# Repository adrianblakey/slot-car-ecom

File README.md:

# The Remora&trade; 1 - Slot Car eCom

This repo contains a [KiCad](https://www.kicad.org/) design, documentation and ancillary artifacts for a slot car brushless motor electronic commutator or "eCom", also known as an Electronic Speed Controller (ESC).

If you are looking for our latest board - the Remora&trade; 2 - you find it here: https://github.com/aartech-dev/Remora2 Please note this is in a different github organization to where we'll eventually move this repo.

All the intellectual property herein is released under a modified [creative commons license](https://github.com/adrianblakey/slot-car-ecom/blob/main/AART_Remora_eCom_License_v1.2.pdf). Under the terms of this license you are free to use everything you find here and make your own eCom from the distributed files as long as you comply with certain rules that are spelled out in the above document. We hope that by doing so we'll stimulate innovation and experimentation. If you have suggestions for improvement please file a bug report and tell us about it. 

There is a [remora1 discussion channel on Discord](https://discord.gg/e3FdfGwk2X) to provide feedback. Also, a good place to get help is the [ESCape32 slot car discord channel](https://discord.gg/XNwYPM7E). ESCape32 is the firmware we have used to run this eCom it's also open source and you'll find it on [github too.](https://github.com/neoxic/ESCape32)

There is nothing stopping you from making your own copies of this eCom. As a hobbyist, or manufacturer everything is here to help you do that. As a hobbyist and with a bit of effort you can make very small quantities at very reasonable cost.

If you choose to manufactuer the parts and sell them as a finished product we ask that you negotiate a small royalty payment with us. These designs are open but not free - all the intellectual property (IP) in this repo. belongs to us. If you have a product you are selling that's based on our IP and it's out there in the marketplace we'll know about it because it's a small (slot car) world. If you are making and selling our designs please talk to us and be up front about it. We incur some real expenses to create this and we want to continue innovating. To do that requires some income and that comes from making parts from the design and selling them.

You should also know that if you are making and selling parts it's your responsibility to support the people who buy them. We are more than happy to help you do that if we are receiving some compensation from you. We've been very generous with the amount of information that we have shared publically on this WiKi to make support simpler. If you choose to republish this information you are under obligation of our [License](https://github.com/adrianblakey/slot-car-ecom/blob/main/AART_Remora_eCom_License_v1.2.pdf) to acknowledge its source. 

We also ask that nothing here is used for military purposes. This also applies to the ESCape32 firmware.

Please refer to the [WiKi for detailed information](https://github.com/adrianblakey/slot-car-ecom/wiki).

Communicate with us on the slot-car channel of the [ESCape32 Discord server.](https://discord.gg/b9SHzh3eSR)

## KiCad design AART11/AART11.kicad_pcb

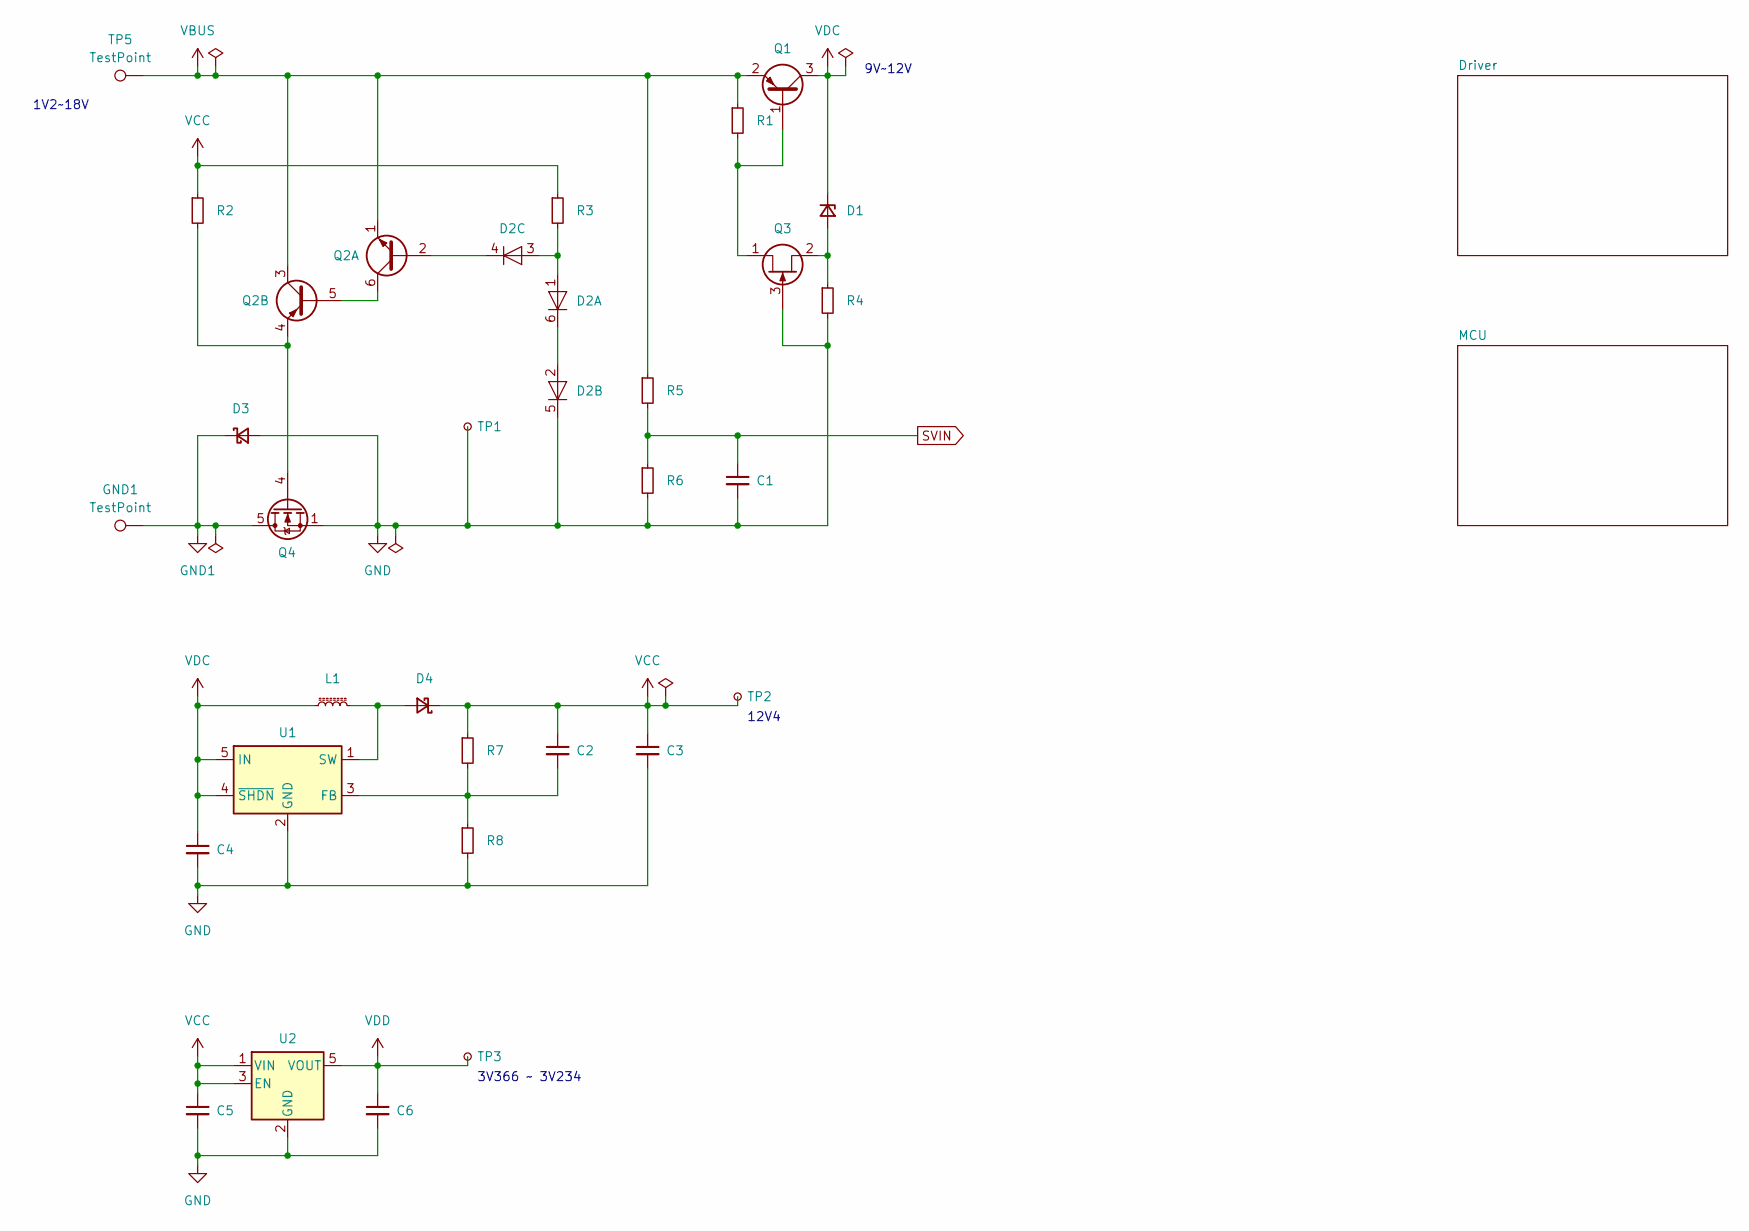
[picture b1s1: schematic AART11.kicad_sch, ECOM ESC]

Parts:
C1: 100nF; C_0402_1005Metric; Rating X7R - 16V - ±10%; JLCPCB Part # C1525
C2: 10pF; C_0402_1005Metric; Rating C0G - 50V - ±5%; JLCPCB Part # C32949
C3, C5: 1uF; C_0603_1608Metric; Rating X5R - 50V - ±10%; JLCPCB Part # C15849
C4, C6: 2.2uF; C_0603_1608Metric; Rating X5R - 16V - ±10%; JLCPCB Part # C23630
D1: BZX584C8V2; D_SOD-523; JLCPCB Part # C2991969
D2: MMBD4448HTW; SOT-363_SC-70-6; JLCPCB Part # C435910
D3: PMEG3030EP; D_SOD-128; JLCPCB Part # C255587
D4: RB521SM-40T2R; D_SOD-523; JLCPCB Part # C253516
GND1: TestPoint; TestPoint_Pad_2.5x2.5mm
L1: 10uH; L_Sunltech_SLW2010P; Rating 750mA - ±20%; JLCPCB Part # C207862
Q1: FMMT718; SOT-23; JLCPCB Part # C2910189
Q2: EMZ1T2R; SOT-563; JLCPCB Part # C510332
Q3: MMBFJ309; SOT-23; JLCPCB Part # C58012
Q4: JMSL0302AU; VSON-8_3.3x3.3mm_P0.65mm_NexFET; JLCPCB Part # C2890409
R1, R5, R8: 10k; R_0402_1005Metric; Rating 62.5mW - ±1%; JLCPCB Part # C25744
R2, R6: 2k2; R_0402_1005Metric; Rating 62.5mW - ±1%; JLCPCB Part # C25879
R3: 4k7; R_0402_1005Metric; Rating 62.5mW - ±1%; JLCPCB Part # C25900
R4: 330R; R_0402_1005Metric; Rating 62.5mW - ±1%; JLCPCB Part # C25104
R7: 91k; R_0402_1005Metric; Rating 62.5mW - ±1%; JLCPCB Part # C4147
TP1, TP2, TP3: TestPoint_Small; TestPoint_Pad_D1.0mm
TP5: TestPoint; TestPoint_Pad_2.5x2.5mm
U1: AP3015KTR-G1; SOT-23-5; JLCPCB Part # C151334
U2: AP2210K-3.3TRG1; SOT-23-5; JLCPCB Part # C176959

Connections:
GND: C1.2, C3.2, C4.2, C5.2, C6.2, D2.5 (K), D3.2 (A), Q3.3 (G), Q4.1 (S), Q4.2 (S), Q4.3 (S), R4.2, R6.2, R8.2, TP1.1, U1.2 (GND), U2.2 (GND); also elsewhere on the board
GND1: D3.1 (K), GND1.1, Q4.5 (D)
unnamed: D1.2 (A), Q3.2 (S), R4.1
unnamed: D2.1 (A), D2.3 (A), R3.2
unnamed: D2.2 (A), D2.6 (K)
unnamed: D2.4 (K), Q2.2 (B1)
unnamed: D4.2 (A), L1.2, U1.1 (SW)
unnamed: Q1.1 (B), Q3.1 (D), R1.2
unnamed: Q2.5 (B2), Q2.6 (C1)
unnamed: Q2.4 (E2), Q4.4 (G), R2.2
unnamed: C2.2, R7.2, R8.1, U1.3 (FB)
SVIN: C1.1, R5.2, R6.1; also elsewhere on the board
VBUS: Q1.2 (E), Q2.1 (E1), Q2.3 (C2), R1.1, R5.1, TP5.1; also elsewhere on the board
VCC: C2.1, C3.1, C5.1, D4.1 (K), R2.1, R3.1, R7.1, TP2.1, U2.1 (VIN), U2.3 (EN); also elsewhere on the board
VDC: C4.1, D1.1 (K), L1.1, Q1.3 (C), U1.4 (~SHDN), U1.5 (IN)
VDD: C6.1, TP3.1, U2.5 (VOUT); also elsewhere on the board

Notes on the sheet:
3V366 ~ 3V234
9V~12V
1V2~18V
12V4

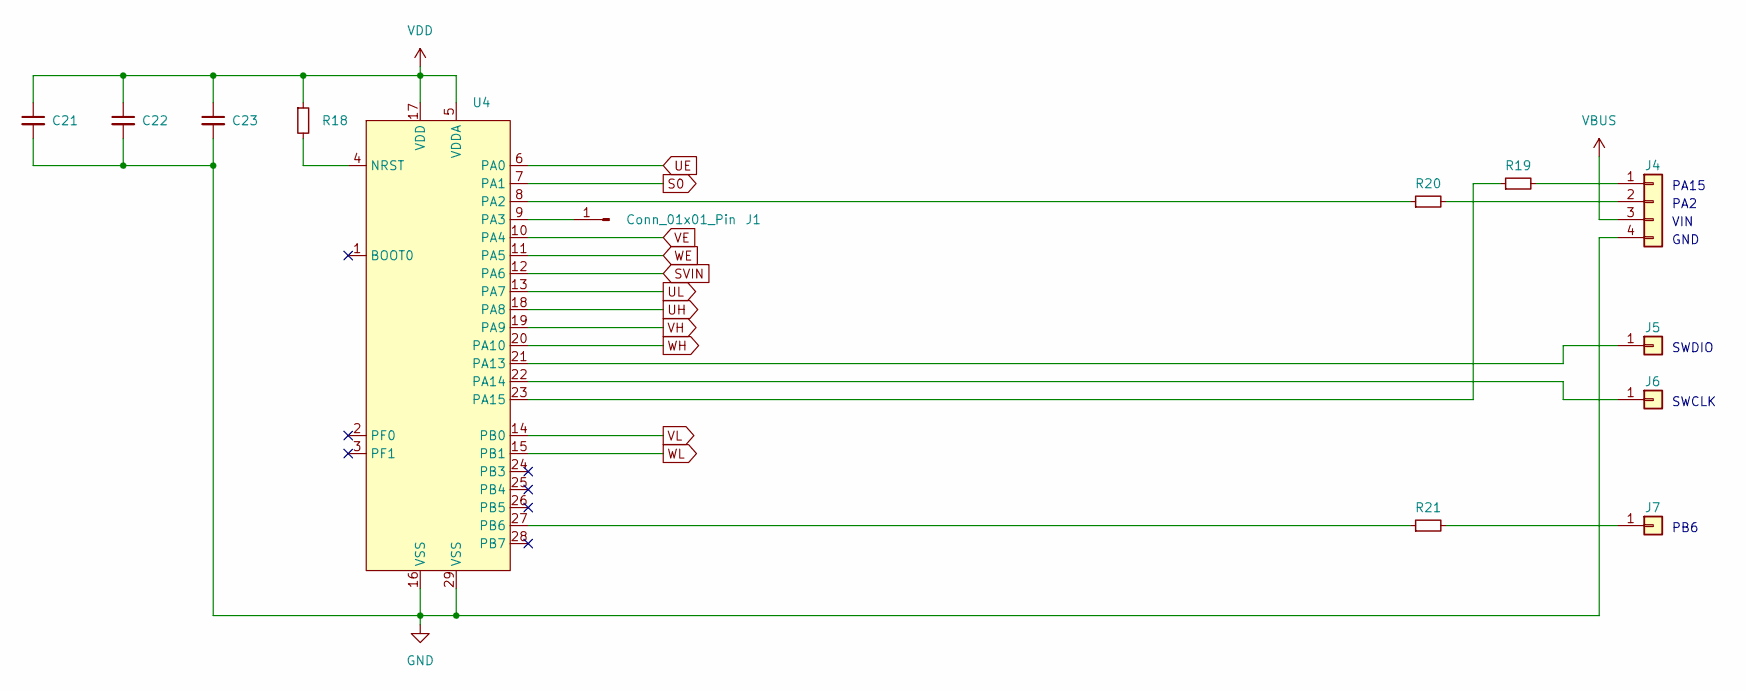
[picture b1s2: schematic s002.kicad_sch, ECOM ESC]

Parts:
C21: 10uF; C_0603_1608Metric; Rating X5R - 25V - ±20%; JLCPCB Part # C96446
C22, C23: 100nF; C_0402_1005Metric; Rating X7R - 16V - ±10%; JLCPCB Part # C1525
J1: Conn_01x01_Pin; Pad0.5
J4: Conn_01x04; HDG 1x04 P0.6 Horizontal; JLCPCB Part # C3008763
J5, J6, J7: Conn_01x01; TestPoint_Pad_1.0x1.0mm
R18: 10k; R_0402_1005Metric; Rating 62.5mW - ±1%; JLCPCB Part # C25744
R19, R20, R21: 1k; R_0402_1005Metric; Rating 62.5mW - ±1%; JLCPCB Part # C11702
U4: AT32F421G8U7; QFN-28-1EP_4x4mm_P0.4mm_EP2.6x2.6mm; JLCPCB Part # C2765098

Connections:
GND: C21.2, C22.2, C23.2, J4.4, U4.16 (VSS), U4.29 (VSS); also elsewhere on the board
unnamed: J1.1, U4.9 (PA3)
unnamed: J4.1, R19.2
unnamed: J4.2, R20.2
unnamed: J5.1, U4.21 (PA13)
unnamed: J6.1, U4.22 (PA14)
unnamed: J7.1, R21.2
unnamed: R18.2, U4.4 (NRST)
unnamed: R20.1, U4.8 (PA2)
unnamed: R19.1, U4.23 (PA15)
unnamed: R21.1, U4.27 (PB6)
S0: U4.7 (PA1); also elsewhere on the board
SVIN: U4.12 (PA6); also elsewhere on the board
UE: U4.6 (PA0); also elsewhere on the board
UH: U4.18 (PA8); also elsewhere on the board
UL: U4.13 (PA7); also elsewhere on the board
VBUS: J4.3; also elsewhere on the board
VDD: C21.1, C22.1, C23.1, R18.1, U4.5 (VDDA), U4.17 (VDD); also elsewhere on the board
VE: U4.10 (PA4); also elsewhere on the board
VH: U4.19 (PA9); also elsewhere on the board
VL: U4.14 (PB0); also elsewhere on the board
WE: U4.11 (PA5); also elsewhere on the board
WH: U4.20 (PA10); also elsewhere on the board
WL: U4.15 (PB1); also elsewhere on the board

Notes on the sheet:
VIN
PA15
SWCLK
PA2
GND
PB6
SWDIO

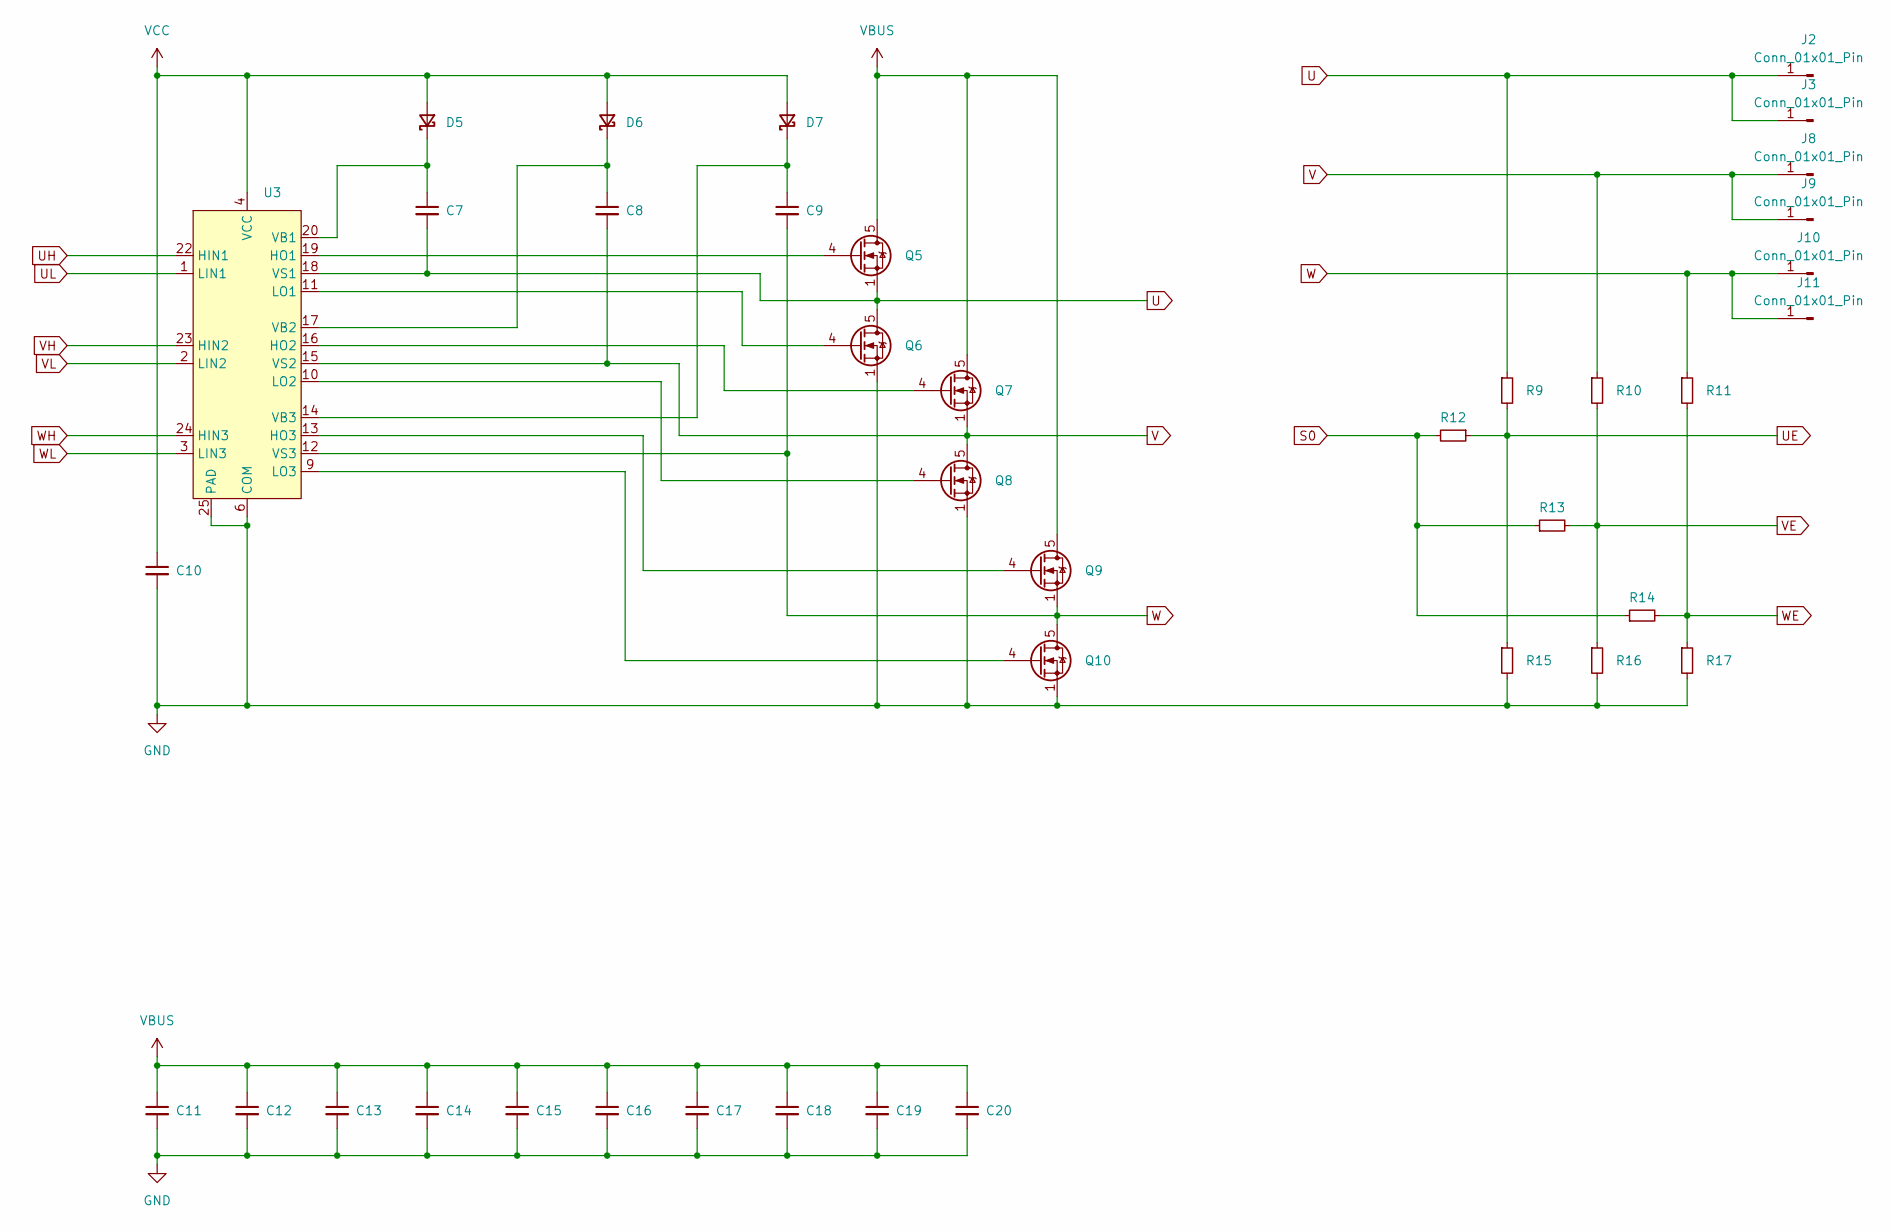
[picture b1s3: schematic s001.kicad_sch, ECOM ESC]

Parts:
C7, C8, C9: 220nF; C_0603_1608Metric; Rating X7R - 25V - ±10%; JLCPCB Part # C21120
C10: 1uF; C_0603_1608Metric; Rating X5R - 50V - ±10%; JLCPCB Part # C15849
C11, C12, C13: 22uF; C_0805_2012Metric; Rating X5R - 25V - ±20%; JLCPCB Part # C45783
C14, C15, C16, C17, C18, C19, C20: 22uF; C_0805_2012Metric_22µF; Rating X5R - 25V - ±20%; JLCPCB Part # C45783
D5, D6, D7: RB521SM-40T2R; D_SOD-523; JLCPCB Part # C253516
J2, J3, J8, J9, J10, J11: Conn_01x01_Pin; SolderWire-0.15sqmm_1x01_D0.5mm_OD1.5mm
Q5, Q6, Q7, Q8, Q9, Q10: JMSL0302AU; VSON-8_3.3x3.3mm_P0.65mm_NexFET; JLCPCB Part # C2890409
R9, R10, R11, R12, R13, R14: 10k; R_0402_1005Metric; Rating 62.5mW - ±1%; JLCPCB Part # C25744
R15, R16, R17: 2k2; R_0402_1005Metric; Rating 62.5mW - ±1%; JLCPCB Part # C25879
U3: FD6288Q; QFN-24-1EP_4x4mm_P0.5mm_EP2.6x2.6mm; JLCPCB Part # C328453

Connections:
GND: C10.2, C11.2, C12.2, C13.2, C14.2, C15.2, C16.2, C17.2, C18.2, C19.2, C20.2, Q6.1 (S), Q6.2 (S), Q6.3 (S), Q8.1 (S), Q8.2 (S), Q8.3 (S), Q10.1 (S), Q10.2 (S), Q10.3 (S), R15.2, R16.2, R17.2, U3.6 (COM), U3.25 (PAD); also elsewhere on the board
unnamed: C7.1, D5.1 (K), U3.20 (VB1)
unnamed: C8.1, D6.1 (K), U3.17 (VB2)
unnamed: C9.1, D7.1 (K), U3.14 (VB3)
unnamed: Q5.4 (G), U3.19 (HO1)
unnamed: Q6.4 (G), U3.11 (LO1)
unnamed: Q7.4 (G), U3.16 (HO2)
unnamed: Q8.4 (G), U3.10 (LO2)
unnamed: Q9.4 (G), U3.13 (HO3)
unnamed: Q10.4 (G), U3.9 (LO3)
S0: R12.2, R13.1, R14.1; also elsewhere on the board
U: C7.2, J2.1, J3.1, Q5.1 (S), Q5.2 (S), Q5.3 (S), Q6.5 (D), R9.1, U3.18 (VS1)
UE: R9.2, R12.1, R15.1; also elsewhere on the board
UH: U3.22 (HIN1); also elsewhere on the board
UL: U3.1 (LIN1); also elsewhere on the board
V: C8.2, J8.1, J9.1, Q7.1 (S), Q7.2 (S), Q7.3 (S), Q8.5 (D), R10.1, U3.15 (VS2)
VBUS: C11.1, C12.1, C13.1, C14.1, C15.1, C16.1, C17.1, C18.1, C19.1, C20.1, Q5.5 (D), Q7.5 (D), Q9.5 (D); also elsewhere on the board
VCC: C10.1, D5.2 (A), D6.2 (A), D7.2 (A), U3.4 (VCC); also elsewhere on the board
VE: R10.2, R13.2, R16.1; also elsewhere on the board
VH: U3.23 (HIN2); also elsewhere on the board
VL: U3.2 (LIN2); also elsewhere on the board
W: C9.2, J10.1, J11.1, Q9.1 (S), Q9.2 (S), Q9.3 (S), Q10.5 (D), R11.1, U3.12 (VS3)
WE: R11.2, R14.2, R17.1; also elsewhere on the board
WH: U3.24 (HIN3); also elsewhere on the board
WL: U3.3 (LIN3); also elsewhere on the board

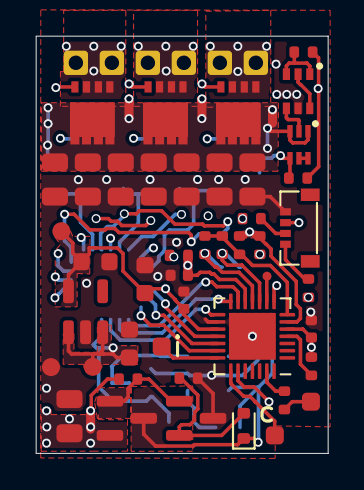
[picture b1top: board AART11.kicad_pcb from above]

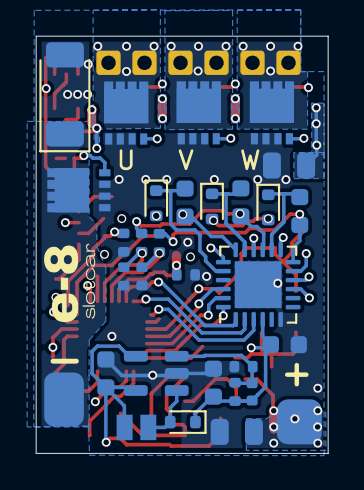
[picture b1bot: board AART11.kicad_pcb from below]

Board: 4 copper layers, 16.2 x 23.2 mm, 83 parts (32 on the bottom side), 48 nets.

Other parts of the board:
e8-logo: e8-logo; e8

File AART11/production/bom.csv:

Comment,Designator,Footprint,JLCPCB Part #
100nF,"C1, C22, C23",402,C1525
1uF,"C10, C3, C5",603,C15849
22uF,"C11, C12, C13, C14, C15, C16, C17, C18, C19, C20",805,C45783
10pF,C2,402,C32949 
10uF,C21,603,C96446
2.2uF,"C4, C6",603,C23630
220nF,"C7, C8, C9",603,C21120
BZX584C8V2,D1,D_SOD-523,C2991969
MMBD4448HTW,D2,SOT-363_SC-70-6,C435910
PMEG3030EP,D3,D_SOD-128,C255587
RB521SM-40T2R,"D4, D5, D6, D7",D_SOD-523,C253516
TestPoint,"GND1, TP5",TestPoint_Pad_2.5x2.5mm,
Conn_01x01_Pin,J1,Pad0.5,
Conn_01x01_Pin,"J10, J11, J2, J3, J8, J9",SolderWire-0.15sqmm_1x01_D0.5mm_OD1.5mm,
Conn_01x04,J4,HDG 1x04 P0.6 Horizontal,C3008763
Conn_01x01,"J5, J6, J7",TestPoint_Pad_1.0x1.0mm,
10uH,L1,L_Sunltech_SLW2010P,C207862
FMMT718,Q1,SOT-23,C2910189
JMSL0302AU,"Q10, Q4, Q5, Q6, Q7, Q8, Q9",VSON-8_3.3x3.3mm_P0.65mm_NexFET,C2890409
EMZ1T2R,Q2,SOT-563,C510332
MMBFJ309,Q3,SOT-23,C58012
10k,"R1, R10, R11, R12, R13, R14, R18, R5, R8, R9",402,C25744
2k2,"R15, R16, R17, R2, R6",402,C25879
1k,"R19, R20, R21",402,C11702
4k7,R3,402,C25900
330R,R4,402,C25104
91k,R7,402,C4147
TestPoint_Small,"TP1, TP2, TP3",TestPoint_Pad_D1.0mm,
AP3015KTR-G1,U1,SOT-23-5,C151334
AP2210K-3.3TRG1,U2,SOT-23-5,C176959
FD6288Q,U3,QFN-24-1EP_4x4mm_P0.5mm_EP2.6x2.6mm,C328453
AT32F421G8U7,U4,QFN-28-1EP_4x4mm_P0.4mm_EP2.6x2.6mm,C2765098

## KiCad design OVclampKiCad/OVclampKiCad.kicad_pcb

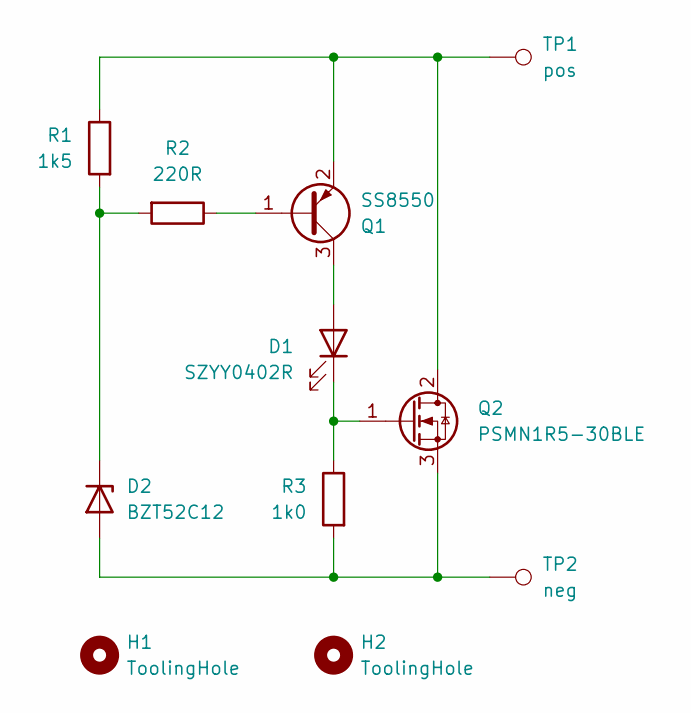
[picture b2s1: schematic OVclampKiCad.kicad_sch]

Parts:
D1: SZYY0402R; LED_0402_1005Metric_ReducedSilkScreen; JLCPCB Part # C434445
D2: BZT52C12; D_SOD-123F_ReducedSilkScreen; JLCPCB Part # C2891780
H1, H2: ToolingHole; ToolingHole_1.152mm
Q1: SS8550; SOT-23.kicad_NoSilkScreen_mod; JLCPCB Part # C8542
Q2: PSMN1R5-30BLE; TO-263-2.kicad_ReducedSilkscreen_mod; JLCPCB Part # C20755573
R1: 1k5; R_0402_1005Metric_NoSilkScreen; JLCPCB Part # C25867
R2: 220R; R_0402_1005Metric_NoSilkScreen; JLCPCB Part # C25091
R3: 1k0; R_0402_1005Metric_NoSilkScreen; JLCPCB Part # C11702
TP1: pos; SolderWirePad_1x01_SMD_5mmx5mm
TP2: neg; SolderWirePad_1x01_SMD_5mmx5mm

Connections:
unnamed: D1.2 (A), Q1.3 (C)
unnamed: D1.1 (K), Q2.1 (G), R3.1
unnamed: D2.2 (A), Q2.3 (S), R3.2, TP2.1
unnamed: D2.1 (K), R1.2, R2.2
unnamed: Q1.1 (B), R2.1
unnamed: Q1.2 (E), Q2.2 (D), R1.1, TP1.1

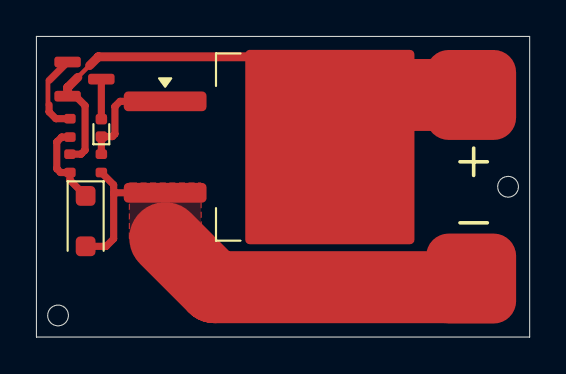
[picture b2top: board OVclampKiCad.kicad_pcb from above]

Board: 2 copper layers, 27.4 x 16.7 mm, 11 parts (0 on the bottom side), 6 nets.

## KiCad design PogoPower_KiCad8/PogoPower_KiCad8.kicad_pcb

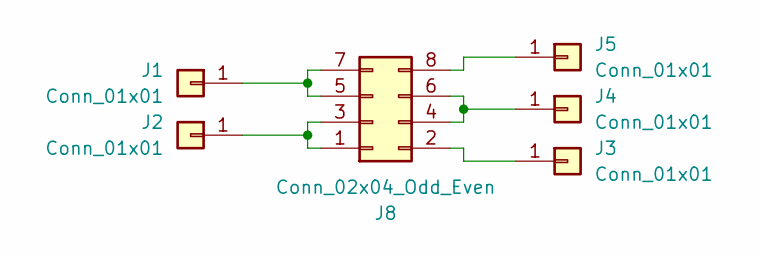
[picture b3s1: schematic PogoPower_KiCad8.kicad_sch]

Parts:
J1, J2, J3, J4, J5: Conn_01x01; PogoRecptacle_D1.4mm_OD2.0mm
J8: Conn_02x04_Odd_Even; PinHeader_2x04_P2.54mm_Vertical

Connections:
unnamed: J1.1, J8.5, J8.7
unnamed: J2.1, J8.1, J8.3
unnamed: J3.1, J8.2
unnamed: J4.1, J8.4, J8.6
unnamed: J5.1, J8.8

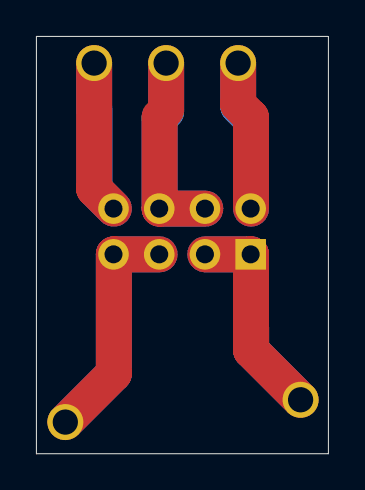
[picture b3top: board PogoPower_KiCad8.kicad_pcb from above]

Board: 2 copper layers, 16.2 x 23.2 mm, 6 parts (1 on the bottom side), 5 nets.

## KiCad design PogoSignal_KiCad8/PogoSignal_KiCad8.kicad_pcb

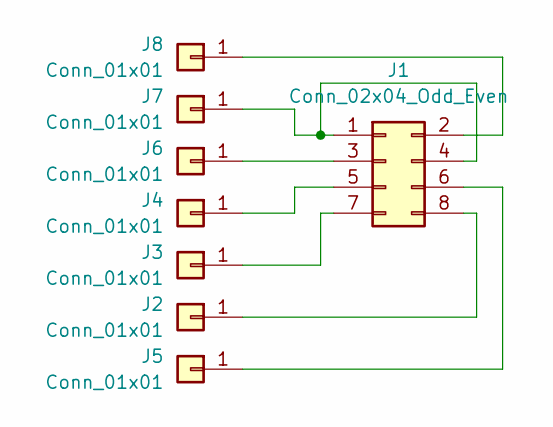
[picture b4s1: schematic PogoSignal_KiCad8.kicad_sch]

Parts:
J1: Conn_02x04_Odd_Even; PinHeader_2x04_P2.54mm_Vertical
J2, J3, J4, J5, J6, J7, J8: Conn_01x01; PogoRecptacle_D1.4mm_OD2.0mm

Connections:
unnamed: J1.1, J1.4, J7.1
unnamed: J1.2, J8.1
unnamed: J1.3, J6.1
unnamed: J1.5, J4.1
unnamed: J1.6, J5.1
unnamed: J1.7, J3.1
unnamed: J1.8, J2.1

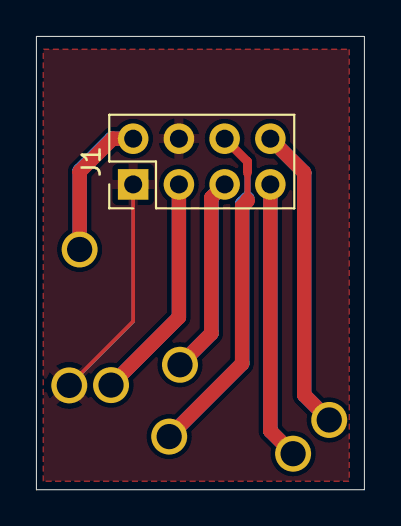
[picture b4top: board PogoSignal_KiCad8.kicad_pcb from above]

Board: 2 copper layers, 18.2 x 25.2 mm, 8 parts (0 on the bottom side), 7 nets.

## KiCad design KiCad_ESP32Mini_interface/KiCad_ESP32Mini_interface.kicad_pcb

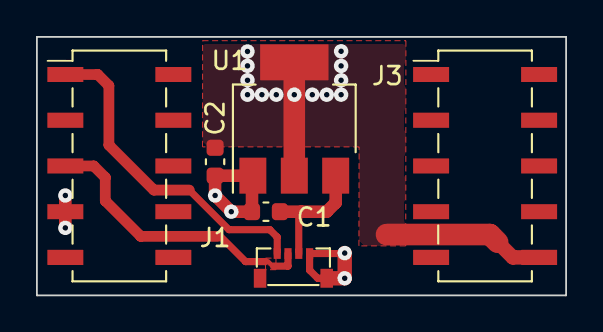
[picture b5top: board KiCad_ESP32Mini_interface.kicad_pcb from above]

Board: 2 copper layers, 29.4 x 14.4 mm, 6 parts (0 on the bottom side), 5 nets.

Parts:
C1, C2: 1µF 50V; C_0603_1608Metric
J1, J3: Conn_02x05_Odd_Even; C843271_PinSocket_2x05_P2.54mm_Vertical_SMD_OddEven
J2: Conn_01x04; HDG 1x04 P0.6 Horizontal
U1: LDL1117S33R_SOT223; SOT-223-3_TabPin2

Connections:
unnamed: J1.1, J2.1
unnamed: J1.5, J2.2
unnamed: C1.2, C2.2, J1.7, J2.4, U1.1 (GND)
unnamed: C1.1, J2.3, U1.3 (VI)
unnamed: C2.1, J3.10, U1.2 (VO)

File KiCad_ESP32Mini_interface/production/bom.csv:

Comment,Designator,Footprint,LCSC Part #
1µF 50V,"C1, C2",603,C15849
Conn_02x05_Odd_Even,"J1, J3",C843271_PinSocket_2x05_P2.54mm_Vertical_SMD_OddEven,C843271
Conn_01x04,J2,HDG 1x04 P0.6 Horizontal,C509242
LDL1117S33R_SOT223,U1,SOT-223-3_TabPin2,C435835

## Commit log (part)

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2023-12-21 Added requirements doc
2023-12-21 More README extracted from telegram
2023-12-21 Add binaries
2023-12-21 Typo
2023-12-25 More updates
2023-12-29 README update
2023-12-29 Remove file
2024-01-03 Upated binaries
2024-01-09 Added test plan
2024-01-26 New rev9, p2 build
2024-01-26 New binaries
2024-01-26 Cleaner
2024-01-26 Clean
2024-02-07 Binaries for debugging
2024-02-25 Updated binaries
2024-02-29 New binary
2024-03-06 Added mini if
2024-03-06 Added if
2024-03-06 Added sim
2024-03-06 gitignore
2024-03-18 Bigger choice of firmware
2024-03-23 Updated binaries w 100% pwm
2024-04-04 new binary selection
2024-04-04 Added png
2024-04-07 Updated v8 fix footprints
2024-04-07 Added inductor fp
2024-04-10 rev11 bins
2024-04-12 New bin
2024-04-15 Update KiCad fix L1
2024-04-15 Rev11 p1
2024-04-17 Update test doc
2024-04-17 JLC png
2024-04-19 Added ss
2024-04-23 Get KiCad right V7
2024-04-23 Added wifi encl
2024-04-23 Better gitigore
2024-04-23 Get bom and posn right
2024-04-29 Move images to own directory
2024-04-29 Image for braking
2024-04-29 Image added
2024-05-01 Added images
2024-05-07 Added hex duty-min
2024-05-14 Updated bin
2024-05-15 Added pkg
2024-05-25 Corrected bin
2024-06-01 Better defaults
2024-06-01 Silly error
2024-06-02 Name change
2024-06-06 Added doug build
2024-06-11 100 duty_spud
2024-06-26 Rev 11 p3
2024-07-06 MA names
2024-07-14 Added flashing boards
2024-09-03 Pogo Power slikscreen
2024-09-11 Better fets
2024-09-16 Added CAD for board carrier
2024-09-27 Staged binaries for test
2024-11-02 Wrong part number
2024-12-05 Gerber for the jig
2025-05-26 Added clamp doc
2025-05-26 Updated requirements, added lid
2025-05-26 Updt gitignore
2025-06-28 Added clamp
2025-06-30 Removed binary distros.
2025-06-30 KiCad 9 update
2025-07-02 Removed images
2025-08-06 Logo update for e8
2025-08-11 A better box
2026-03-10 incr freq limit 72 144
2026-03-10 Update README with details on experimental binaries
    Added information about the experimental binaries and their capabilities.
2026-03-19 High pwm freq binaries for high Kv motors
2026-03-20 The freq fixes
2026-04-20 Added a license
